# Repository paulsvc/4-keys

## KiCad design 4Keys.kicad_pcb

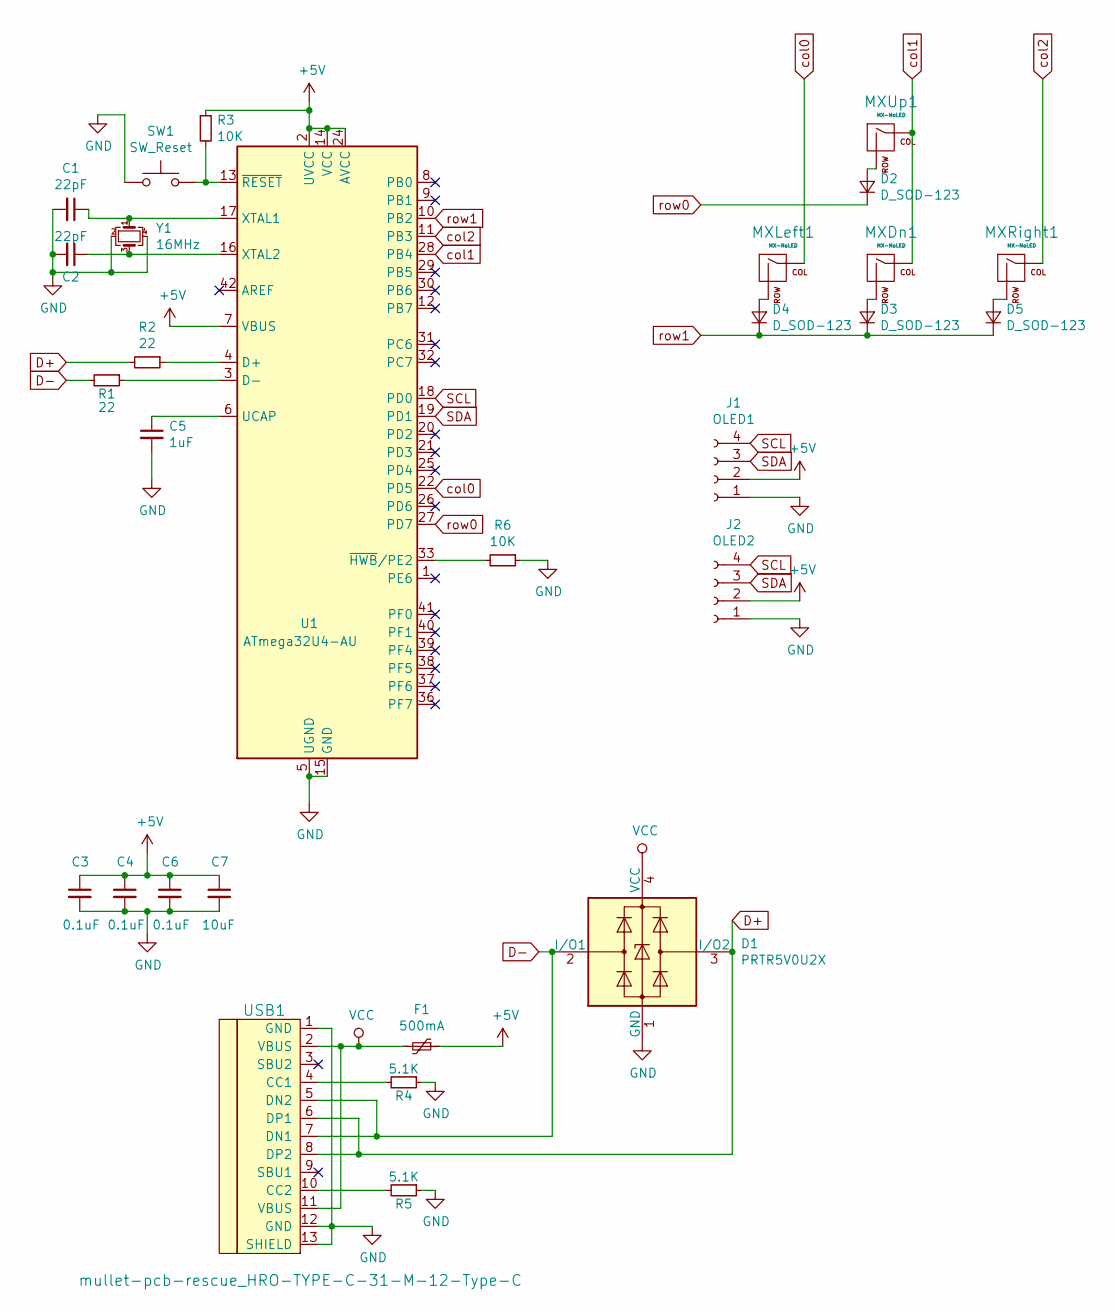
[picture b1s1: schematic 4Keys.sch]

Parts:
C1, C2: 22pF; C_0805_2012Metric
C3, C4, C6: 0.1uF; C_0805_2012Metric
C5: 1uF; C_0805_2012Metric
C7: 10uF; C_0805_2012Metric
D1: PRTR5V0U2X; SOT-143
D2, D3, D4, D5: D_SOD-123; D_0805_2012Metric
F1: 500mA; Fuse_1206_3216Metric
J1: OLED1; JST_EH_S4B-EH_1x04_P2.50mm_Horizontal
J2: OLED2; JST_EH_S4B-EH_1x04_P2.50mm_Horizontal
MXDn1: MX-NoLED; MXOnly-1U-Hotswap
MXLeft1: MX-NoLED; MXOnly-1U-Hotswap
MXRight1: MX-NoLED; MXOnly-1U-Hotswap
MXUp1: MX-NoLED; MXOnly-1U-Hotswap
R1, R2: 22; R_0805_2012Metric
R3, R6: 10K; R_0805_2012Metric
R4, R5: 5.1K; R_0805_2012Metric
SW1: SW_Reset; SKQG-1155865
U1: ATmega32U4-AU; TQFP-44_10x10mm_P0.8mm
USB1: mullet-pcb-rescue_HRO-TYPE-C-31-M-12-Type-C; HRO-TYPE-C-31-M-12-HandSoldering
Y1: 16MHz; Crystal_SMD_3225-4Pin_3.2x2.5mm

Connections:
+5V: C3.1, C4.1, C6.1, C7.1, F1.1, J1.2, J2.2, R3.1, U1.2 (UVCC), U1.7 (VBUS), U1.14 (VCC), U1.24 (AVCC), U1.34 (VCC), U1.44 (AVCC)
D+: D1.3 (I/O2), R2.2, USB1.6 (DP1), USB1.8 (DP2)
D-: D1.2 (I/O1), R1.2, USB1.5 (DN2), USB1.7 (DN1)
GND: C1.2, C2.2, C3.2, C4.2, C5.2, C6.2, C7.2, D1.1 (GND), J1.1, J2.1, R4.1, R5.1, R6.1, SW1.1, U1.5 (UGND), U1.15 (GND), U1.23 (GND), U1.35 (GND), U1.43 (GND), USB1.1 (GND), USB1.12 (GND), USB1.13 (SHIELD), Y1.2, Y1.4
unnamed: C1.1, U1.17 (XTAL1), Y1.1
unnamed: C2.1, U1.16 (XTAL2), Y1.3
unnamed: C5.1, U1.6 (UCAP)
unnamed: D2.2 (A), MXUp1.2 (ROW)
unnamed: D3.2 (A), MXDn1.2 (ROW)
unnamed: D4.2 (A), MXLeft1.2 (ROW)
unnamed: D5.2 (A), MXRight1.2 (ROW)
unnamed: R1.1, U1.3 (D-)
unnamed: R2.1, U1.4 (D+)
unnamed: R3.2, SW1.2, U1.13 (~RESET)
unnamed: R4.2, USB1.4 (CC1)
unnamed: R5.2, USB1.10 (CC2)
unnamed: R6.2, U1.33 (~HWB~/PE2)
SCL: J1.4, J2.4, U1.18 (PD0)
SDA: J1.3, J2.3, U1.19 (PD1)
VCC: D1.4 (VCC), F1.2, USB1.2 (VBUS), USB1.11 (VBUS)
col0: MXLeft1.1 (COL), U1.22 (PD5)
col1: MXDn1.1 (COL), MXUp1.1 (COL), U1.28 (PB4)
col2: MXRight1.1 (COL), U1.11 (PB3)
row0: D2.1 (K), U1.27 (PD7)
row1: D3.1 (K), D4.1 (K), D5.1 (K), U1.10 (PB2)

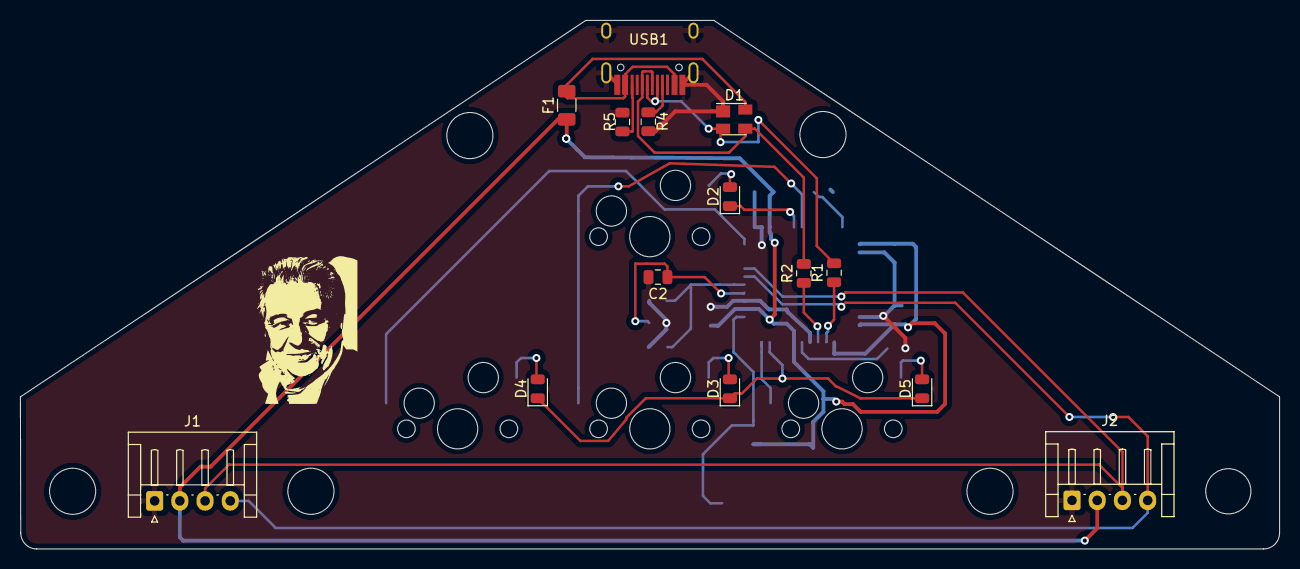
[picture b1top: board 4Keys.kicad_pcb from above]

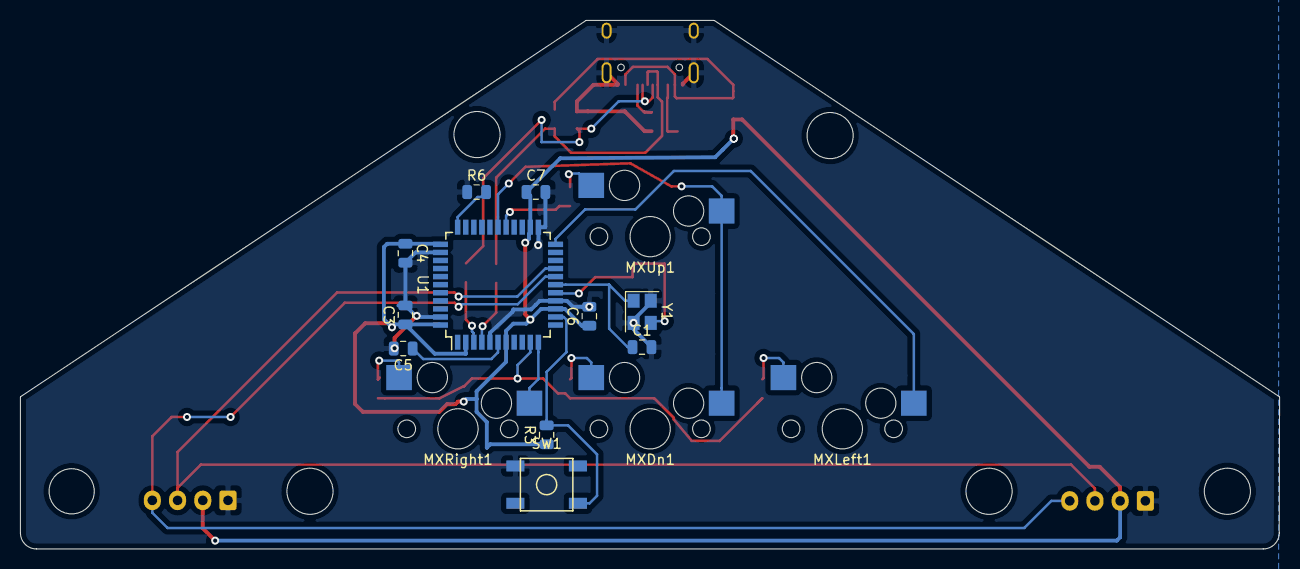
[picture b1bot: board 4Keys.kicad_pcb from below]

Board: 2 copper layers, 124.8 x 52.4 mm, 29 parts (11 on the bottom side), 25 nets.

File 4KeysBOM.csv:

Comment;Designator;Footprint;LCSC
22pF;C1,C2;Capacitor_SMD:C_0805_2012Metric;
0.1uF;C3,C4,C6;Capacitor_SMD:C_0805_2012Metric;
1uF;C5;Capacitor_SMD:C_0805_2012Metric;
10uF;C7;Capacitor_SMD:C_0805_2012Metric;
PRTR5V0U2X;D1;Package_TO_SOT_SMD:SOT-143;
D_SOD-123;D2,D4,D3,D5;Diode_SMD:D_0805_2012Metric;
500mA;F1;Fuse:Fuse_1206_3216Metric;
OLED1;J1;Connector_JST:JST_EH_S4B-EH_1x04_P2.50mm_Horizontal;
OLED2;J2;Connector_JST:JST_EH_S4B-EH_1x04_P2.50mm_Horizontal;
MX-NoLED;MXLeft1,MXDn1,MXRight1,MXUp1;MX_Only:MXOnly-1U-Hotswap;
22;R2,R1;Resistor_SMD:R_0805_2012Metric;
5.1K;R4,R5;Resistor_SMD:R_0805_2012Metric;
10K;R6,R3;Resistor_SMD:R_0805_2012Metric;
SW_Reset;SW1;random-keyboard-parts:SKQG-1155865;
ATmega32U4-AU;U1;Package_QFP:TQFP-44_10x10mm_P0.8mm;
mullet-pcb-rescue_HRO-TYPE-C-31-M-12-Type-C;USB1;mullet:HRO-TYPE-C-31-M-12-HandSoldering;
16MHz;Y1;Crystal:Crystal_SMD_3225-4Pin_3.2x2.5mm;

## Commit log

2020-03-24 UPDATE PCB
2020-03-25 Hotswap
2020-03-25 Updqte PCB V1
2020-03-25 Updqte logo CC
